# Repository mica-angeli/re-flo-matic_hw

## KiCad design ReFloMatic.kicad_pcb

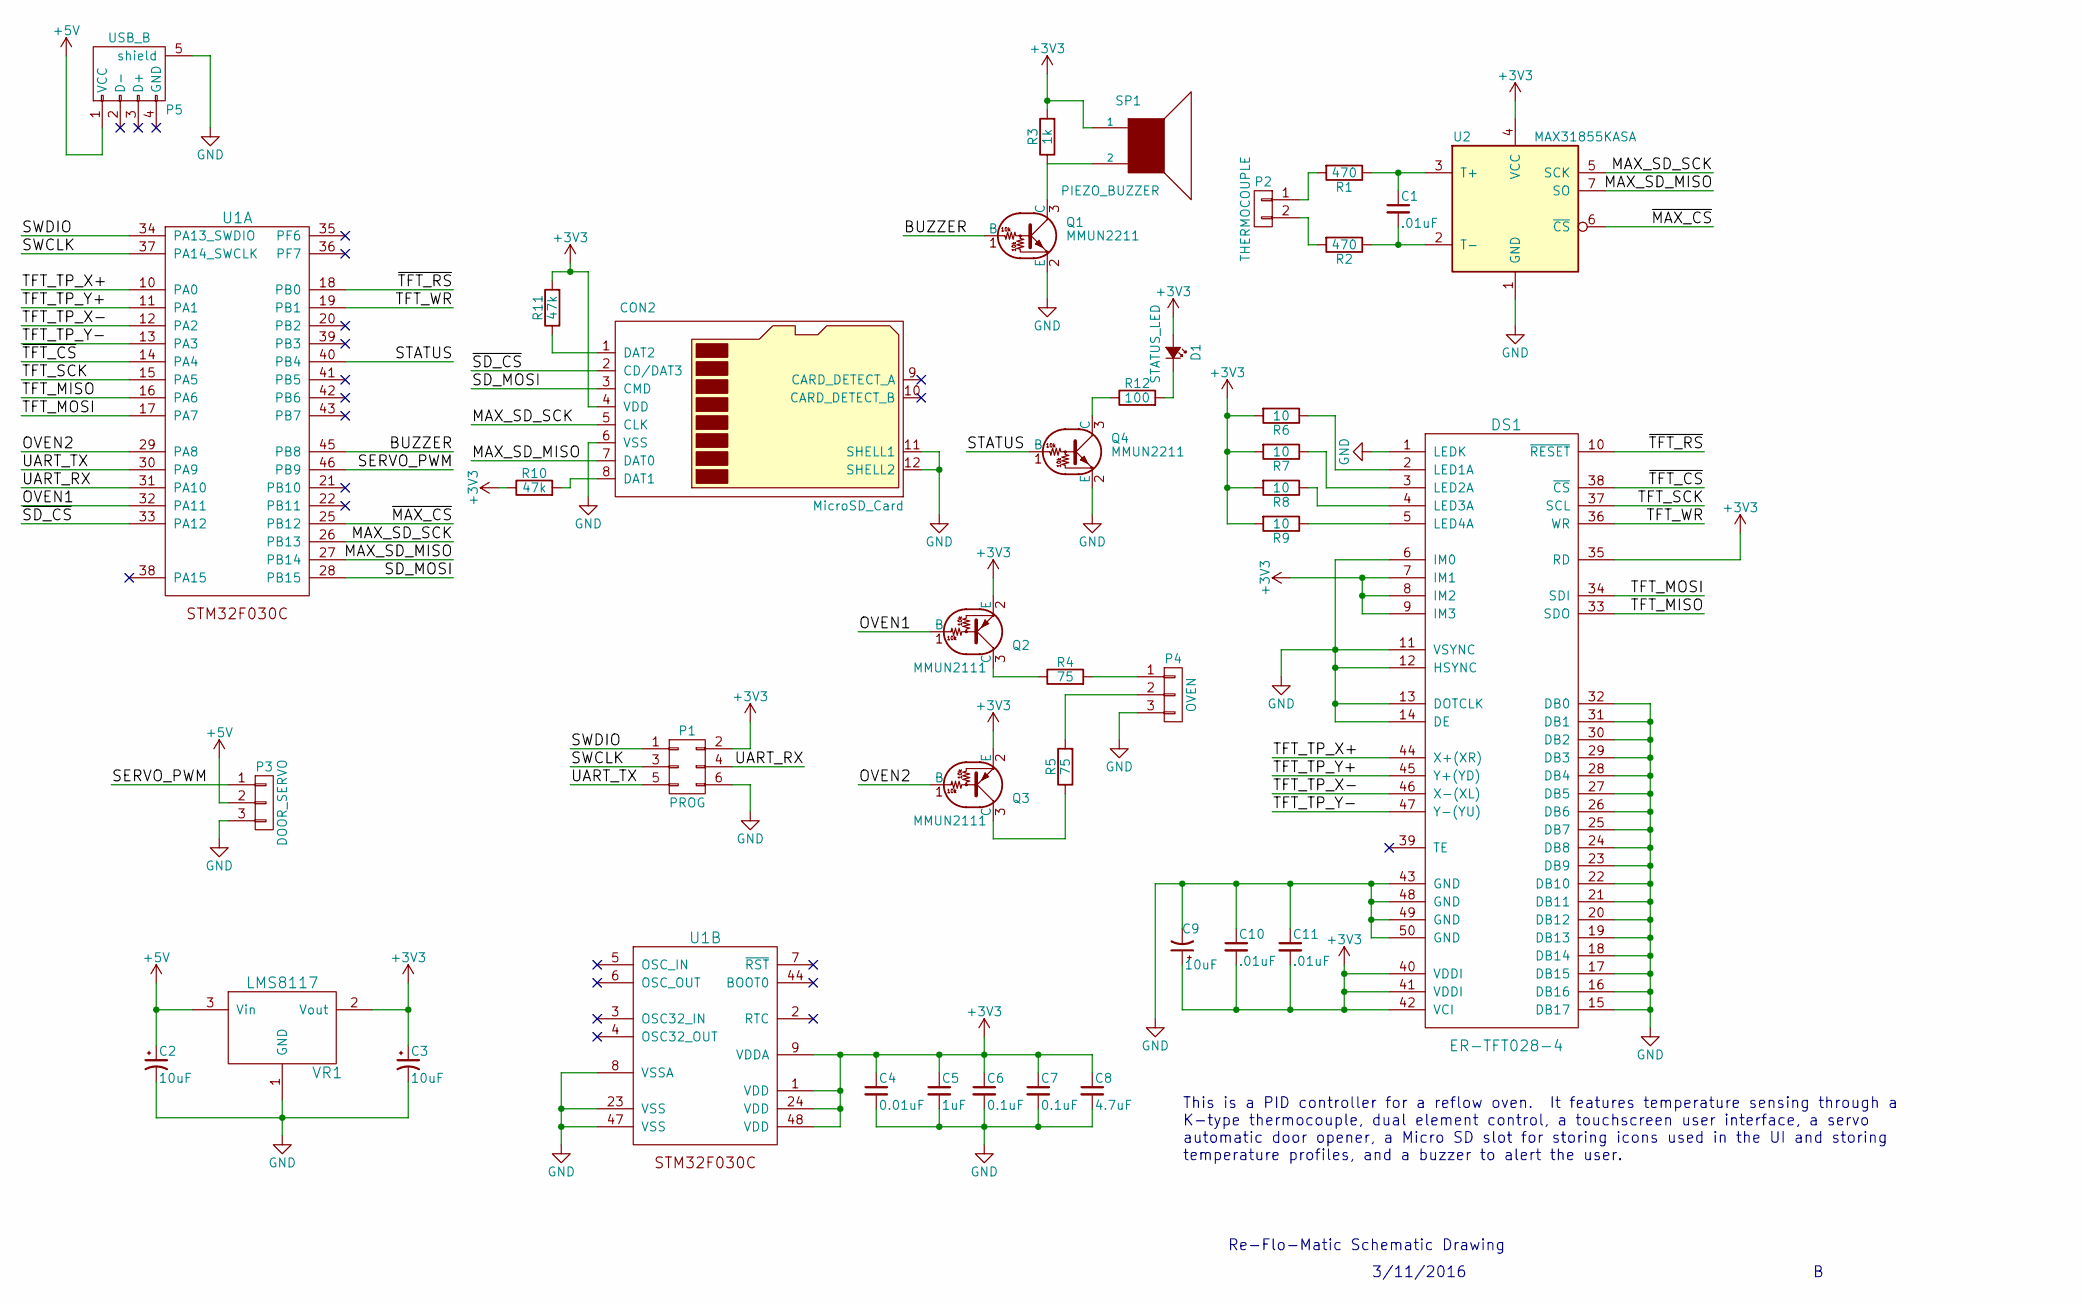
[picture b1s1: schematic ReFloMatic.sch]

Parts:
C1, C10, C11: .01uF; C_0805
C2, C3, C9: 10uF; SMD-1206_Pol
C4: 0.01uF; C_0805
C5: 1uF; C_0805
C6, C7: 0.1uF; C_0805
C8: 4.7uF; C_0805
CON2: MicroSD_Card; DM3D-SF
D1: STATUS_LED; LED_0805
DS1: ER-TFT028-4
P1: PROG; HEADER_2X3_SMD
P2: THERMOCOUPLE; TERMINAL-BLOCK-3.5MM-2POS
P3: DOOR_SERVO; HEADER_1X3_SMD
P4: OVEN; TERMINAL-BLOCK-3.5MM-3POS
P5: USB_B; SMT-Micro-USB-AB
Q1, Q4: MMUN2211; SOT-23
Q2, Q3: MMUN2111; SOT-23
R1, R2: 470; R_0805
R3: 1k; R_0805
R4, R5: 75; R_0805
R6, R7, R8, R9: 10; R_0805
R10, R11: 47k; R_0805
R12: 100; R_0805
SP1: PIEZO_BUZZER; PS1240P02BT
U1: STM32F030C; LQFP-48_7x7mm_Pitch0.5mm
U2: MAX31855KASA; SO-8
VR1: LMS8117; SOT-223

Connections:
+3V3: C3.1, C4.1, C5.1, C6.1, C7.1, C8.1, C9.1, C10.2, C11.2, CON2.4 (VDD), D1.2 (A), DS1.7 (IM1), DS1.8 (IM2), DS1.9 (IM3), DS1.35 (RD), DS1.40 (VDDI), DS1.41 (VDDI), DS1.42 (VCI), P1.2, Q2.2 (E), Q3.2 (E), R3.2, R6.2, R7.2, R8.2, R9.2, R10.1, R11.2, SP1.1, U1.1 (VDD), U1.9 (VDDA), U1.24 (VDD), U1.48 (VDD), U2.4 (VCC), VR1.2 (Vout), VR1.4; also elsewhere on the board
+5V: C2.1, P3.2, P5.1 (VCC), VR1.3 (Vin); also elsewhere on the board
/BUZZER: Q1.1 (B), U1.45 (PB8)
/MAX_SD_MISO: CON2.7 (DAT0), U1.27 (PB14), U2.7 (SO)
/MAX_SD_SCK: CON2.5 (CLK), U1.26 (PB13), U2.5 (SCK)
/OVEN1: Q2.1 (B), U1.32 (PA11)
/OVEN2: Q3.1 (B), U1.29 (PA8)
/SD_MOSI: CON2.3 (CMD), U1.28 (PB15)
/SERVO_PWM: P3.1, U1.46 (PB9)
/STATUS: Q4.1 (B), U1.40 (PB4)
/SWCLK: P1.3, U1.37 (PA14_SWCLK)
/SWDIO: P1.1, U1.34 (PA13_SWDIO)
/TFT_MISO: DS1.33 (SDO), U1.16 (PA6); also elsewhere on the board
/TFT_MOSI: DS1.34 (SDI), U1.17 (PA7); also elsewhere on the board
/TFT_SCK: DS1.37 (SCL), U1.15 (PA5); also elsewhere on the board
/TFT_TP_X+: DS1.44 (X+(XR)), U1.10 (PA0); also elsewhere on the board
/TFT_TP_X-: DS1.46 (X-(XL)), U1.12 (PA2); also elsewhere on the board
/TFT_TP_Y+: DS1.45 (Y+(YD)), U1.11 (PA1); also elsewhere on the board
/TFT_TP_Y-: DS1.47 (Y-(YU)), U1.13 (PA3); also elsewhere on the board
/TFT_WR: DS1.36 (WR), U1.19 (PB1); also elsewhere on the board
/UART_RX: P1.4, U1.31 (PA10)
/UART_TX: P1.5, U1.30 (PA9)
/~MAX_CS: U1.25 (PB12), U2.6 (~CS~)
/~SD_CS: CON2.2 (CD/DAT3), U1.33 (PA12)
/~TFT_CS: DS1.38 (~CS), U1.14 (PA4); also elsewhere on the board
/~TFT_RS: DS1.10 (~RESET), U1.18 (PB0); also elsewhere on the board
GND: C2.2, C3.2, C4.2, C5.2, C6.2, C7.2, C8.2, C9.2, C10.1, C11.1, CON2.6 (VSS), CON2.11 (SHELL1), CON2.12 (SHELL2), DS1.0, DS1.1 (LEDK), DS1.6 (IM0), DS1.11 (VSYNC), DS1.12 (HSYNC), DS1.13 (DOTCLK), DS1.14 (DE), DS1.15 (DB17), DS1.16 (DB16), DS1.17 (DB15), DS1.18 (DB14), DS1.19 (DB13), DS1.20 (DB12), DS1.21 (DB11), DS1.22 (DB10), DS1.23 (DB9), DS1.24 (DB8), DS1.25 (DB7), DS1.26 (DB6), DS1.27 (DB5), DS1.28 (DB4), DS1.29 (DB3), DS1.30 (DB2), DS1.31 (DB1), DS1.32 (DB0), DS1.43 (GND), DS1.48 (GND), DS1.49 (GND), DS1.50 (GND), P1.6, P3.3, P4.3, P5.5 (shield), Q1.2 (E), Q4.2 (E), U1.8 (VSSA), U1.23 (VSS), U1.47 (VSS), U2.1 (GND), VR1.1 (GND); also elsewhere on the board
unnamed: C1.1, R1.1, U2.3 (T+)
unnamed: C1.2, R2.1, U2.2 (T-)
unnamed: CON2.1 (DAT2), R11.1
unnamed: CON2.8 (DAT1), R10.2
unnamed: D1.1 (K), R12.2
unnamed 34: DS1.2 (LED1A), R6.1; also elsewhere on the board
unnamed 35: DS1.3 (LED2A), R7.1; also elsewhere on the board
unnamed 36: DS1.4 (LED3A), R8.1; also elsewhere on the board
unnamed 37: DS1.5 (LED4A), R9.1; also elsewhere on the board
unnamed 38: DS1.39 (TE); also elsewhere on the board
unnamed: P2.1, R1.2
unnamed: P2.2, R2.2
unnamed: P4.1, R4.2
unnamed: P4.2, R5.2
unnamed: Q1.3 (C), R3.1, SP1.2
unnamed: Q2.3 (C), R4.1
unnamed: Q3.3 (C), R5.1
unnamed: Q4.3 (C), R12.1

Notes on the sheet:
This is a PID controller for a reflow oven. It features temperature sensing through a K-type thermocouple, dual element control, a touchscreen user interface, a servo automatic door opener, a Micro SD slot for storing icons used in the UI and storing temperature profiles, and a buzzer to alert the 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
Re-Flo-Matic Schematic Drawing
3/11/2016

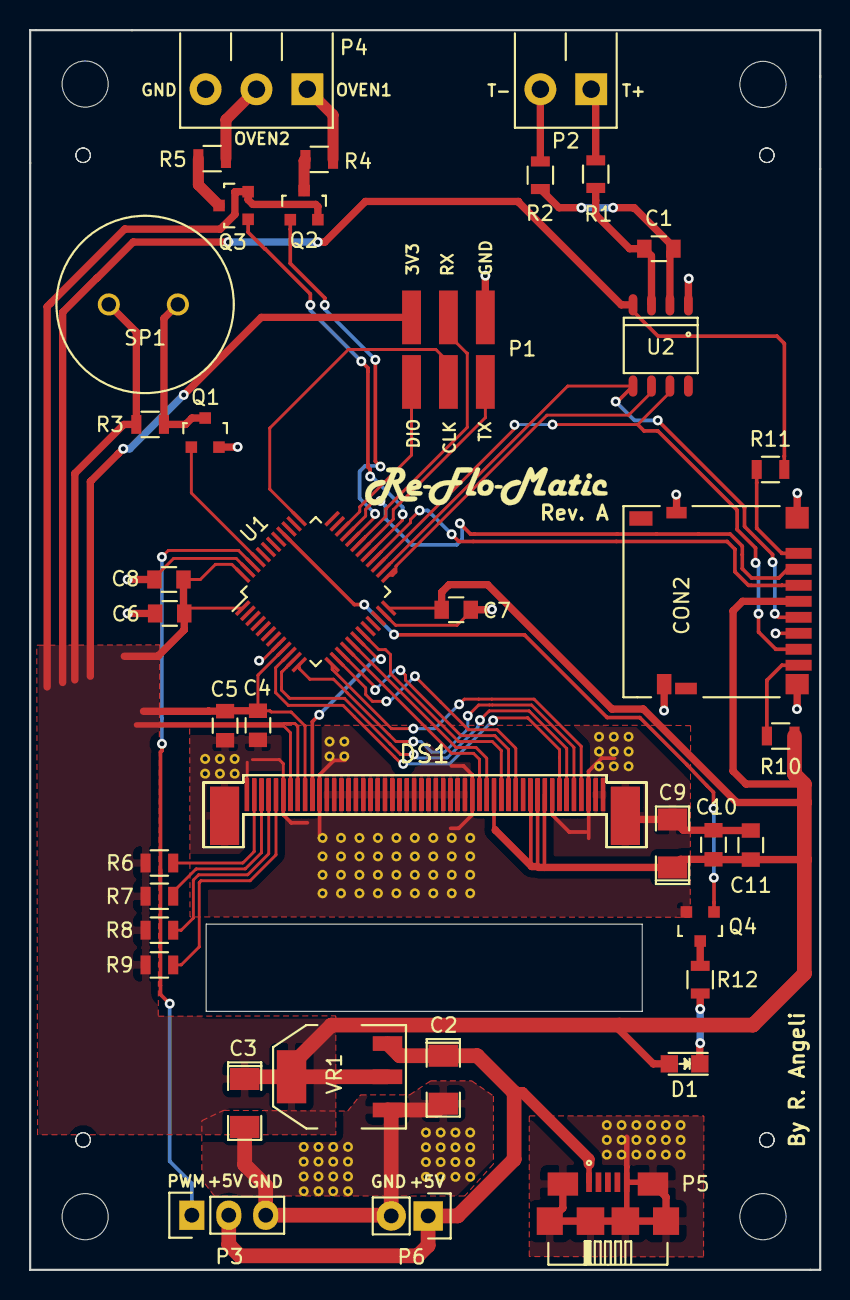
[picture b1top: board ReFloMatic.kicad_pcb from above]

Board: 2 copper layers, 54.4 x 85.3 mm, 41 parts (0 on the bottom side), 45 nets.

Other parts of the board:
DS1#2: ER-TFT028-4
P6: PWR_CONN; Pin_Header_Straight_1x02

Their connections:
+3V3: DS1#2.7, DS1#2.8, DS1#2.9, DS1#2.35, DS1#2.40, DS1#2.41, DS1#2.42; also elsewhere on the board
+5V: P6.1; also elsewhere on the board
/TFT_MISO: DS1#2.33; also elsewhere on the board
/TFT_MOSI: DS1#2.34; also elsewhere on the board
/TFT_SCK: DS1#2.37; also elsewhere on the board
/TFT_TP_X+: DS1#2.44; also elsewhere on the board
/TFT_TP_X-: DS1#2.46; also elsewhere on the board
/TFT_TP_Y+: DS1#2.45; also elsewhere on the board
/TFT_TP_Y-: DS1#2.47; also elsewhere on the board
/TFT_WR: DS1#2.36; also elsewhere on the board
/~TFT_CS: DS1#2.38; also elsewhere on the board
/~TFT_RS: DS1#2.10; also elsewhere on the board
GND: DS1#2.0, DS1#2.1, DS1#2.6, DS1#2.11, DS1#2.12, DS1#2.13, DS1#2.14, DS1#2.15, DS1#2.16, DS1#2.17, DS1#2.18, DS1#2.19, DS1#2.20, DS1#2.21, DS1#2.22, DS1#2.23, DS1#2.24, DS1#2.25, DS1#2.26, DS1#2.27, DS1#2.28, DS1#2.29, DS1#2.30, DS1#2.31, DS1#2.32, DS1#2.43, DS1#2.48, DS1#2.49, DS1#2.50, P6.2; also elsewhere on the board
unnamed 34: DS1#2.2; also elsewhere on the board
unnamed 35: DS1#2.3; also elsewhere on the board
unnamed 36: DS1#2.4; also elsewhere on the board
unnamed 37: DS1#2.5; also elsewhere on the board
unnamed 38: DS1#2.39; also elsewhere on the board

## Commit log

2016-03-04 Finished STM32 schematic drawing.
2016-03-05 Started schematic. Wired up MAX31855 and TFT connector.
2016-03-05 Added buzzer and oven connector.
2016-03-05 Finished Rev. A schematic.
2016-03-06 Started assigning component footprints.
2016-03-06 Started assigning components.
2016-03-12 Added Micro SD card connector. Changed some component values. Began schematic rev B
2016-03-12 Finished Rev. B of schematic.
2016-03-13 Painstakingly created micro sd card footprint and 3D model to match.
2016-03-13 Finished associating all parts and creating all footprints and 3D models. Minor changes to schematic. Started layout.
2016-03-13 Added TFT footprint that contains display and PCB cutout.
2016-03-13 Preliminary component placement.
2016-03-14 Began routing.
2016-03-14 Routing mostly done. Still need to route TFT traces.
2016-03-14 Finished layout.
2016-03-14 Added logo.
2016-03-14 Finished PCB layout. Generated gerbers.
2016-03-14 Changed internal cutout to board edge layer. Regenerated gerbers. Ordered PCB.
